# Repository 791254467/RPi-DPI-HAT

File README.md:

# RPi-DPI-HAT
Raspberry Pi HAT (Hardware Attached on Top) for TFT-Displays with DPI (Display Parallel Interface).

## Shop
* [RPi-DPI-HAT for TFT-Displays](http://www.watterott.com/en/RPi-DPI-HAT)
* [40-Pin FFC-Cable Extenter](http://www.watterott.com/en/40-Pin-FFC-extenter)
* [Bundle: RPi-DPI-HAT + 5" 800x480 Display without Touchpanel](http://www.watterott.com/en/5-800x480-RPi-DPI-HAT)
* Compatible TFT-Displays (Touchpanel cannot be used):
  * [5" 800x480 Display without Touchpanel](http://www.watterott.com/en/5-800x480-TFT-Display-without-TP)
  * [5" 800x480 Display with resitive Touchpanel](http://www.watterott.com/en/5-800x480-TFT-Display)
  * [7" 800x480 Display with resitive Touchpanel](http://www.watterott.com/en/7-800x480-TFT-Display)

## Features
* 40pin connector for TFT-Display
* LED Backlight Boost Regulator (up to 35V)
* Single 5V Power Supply via GPIO connector
* Note: The HDMI and video output cannot be used at the same time with a DPI display.

## Hardware
* [Schematics + Layout](https://github.com/watterott/RPi-DPI-HAT/tree/master/hardware)

## Software
* Install device tree blob ([originally from Robert Ely](https://github.com/robertely/dpi666)):
    ```
    $ sudo apt-get install device-tree-compiler
    $ wget -N https://raw.github.com/watterott/RPi-DPI-HAT/master/docu/dt-blob-dpi.dts
    $ sudo dtc -I dts -O dtb -o /boot/dt-blob.bin dt-blob-dpi.dts
    ```

* Open the file ```/boot/config.txt``` and add the following lines at the file end:
    ```
    $ sudo nano /boot/config.txt
    ```
    ```
    # disable SPI and I2C
    dtparam=spi=off
    dtparam=i2c_arm=off
    
    # enable 800x480 display (TFT050-3, TFT070-4)
    enable_dpi_lcd=1
    display_default_lcd=1
    dpi_group=2
    dpi_mode=87
    dpi_output_format=454661
    hdmi_ignore_edid=0xa5000080
    hdmi_cvt=800 480 60 6 0 0 0
    
    # 0 degrees - normal
    #display_rotate=0
    # 90 degrees
    #display_rotate=1
    # 180 degrees
    #display_rotate=2
    # 270 degrees
    #display_rotate=3
    # horizontal flip
    #display_rotate=0x10000
    # vertical flip
    #display_rotate=0x20000
    ```

* Reboot the system:
    ```
    $ sudo reboot
    ```

    *If there are problems then check, that you have not bootloader version 1.20150923, which has a bug. Upgrade the system with ```sudo apt-get update``` and ```sudo apt-get upgrade```.*

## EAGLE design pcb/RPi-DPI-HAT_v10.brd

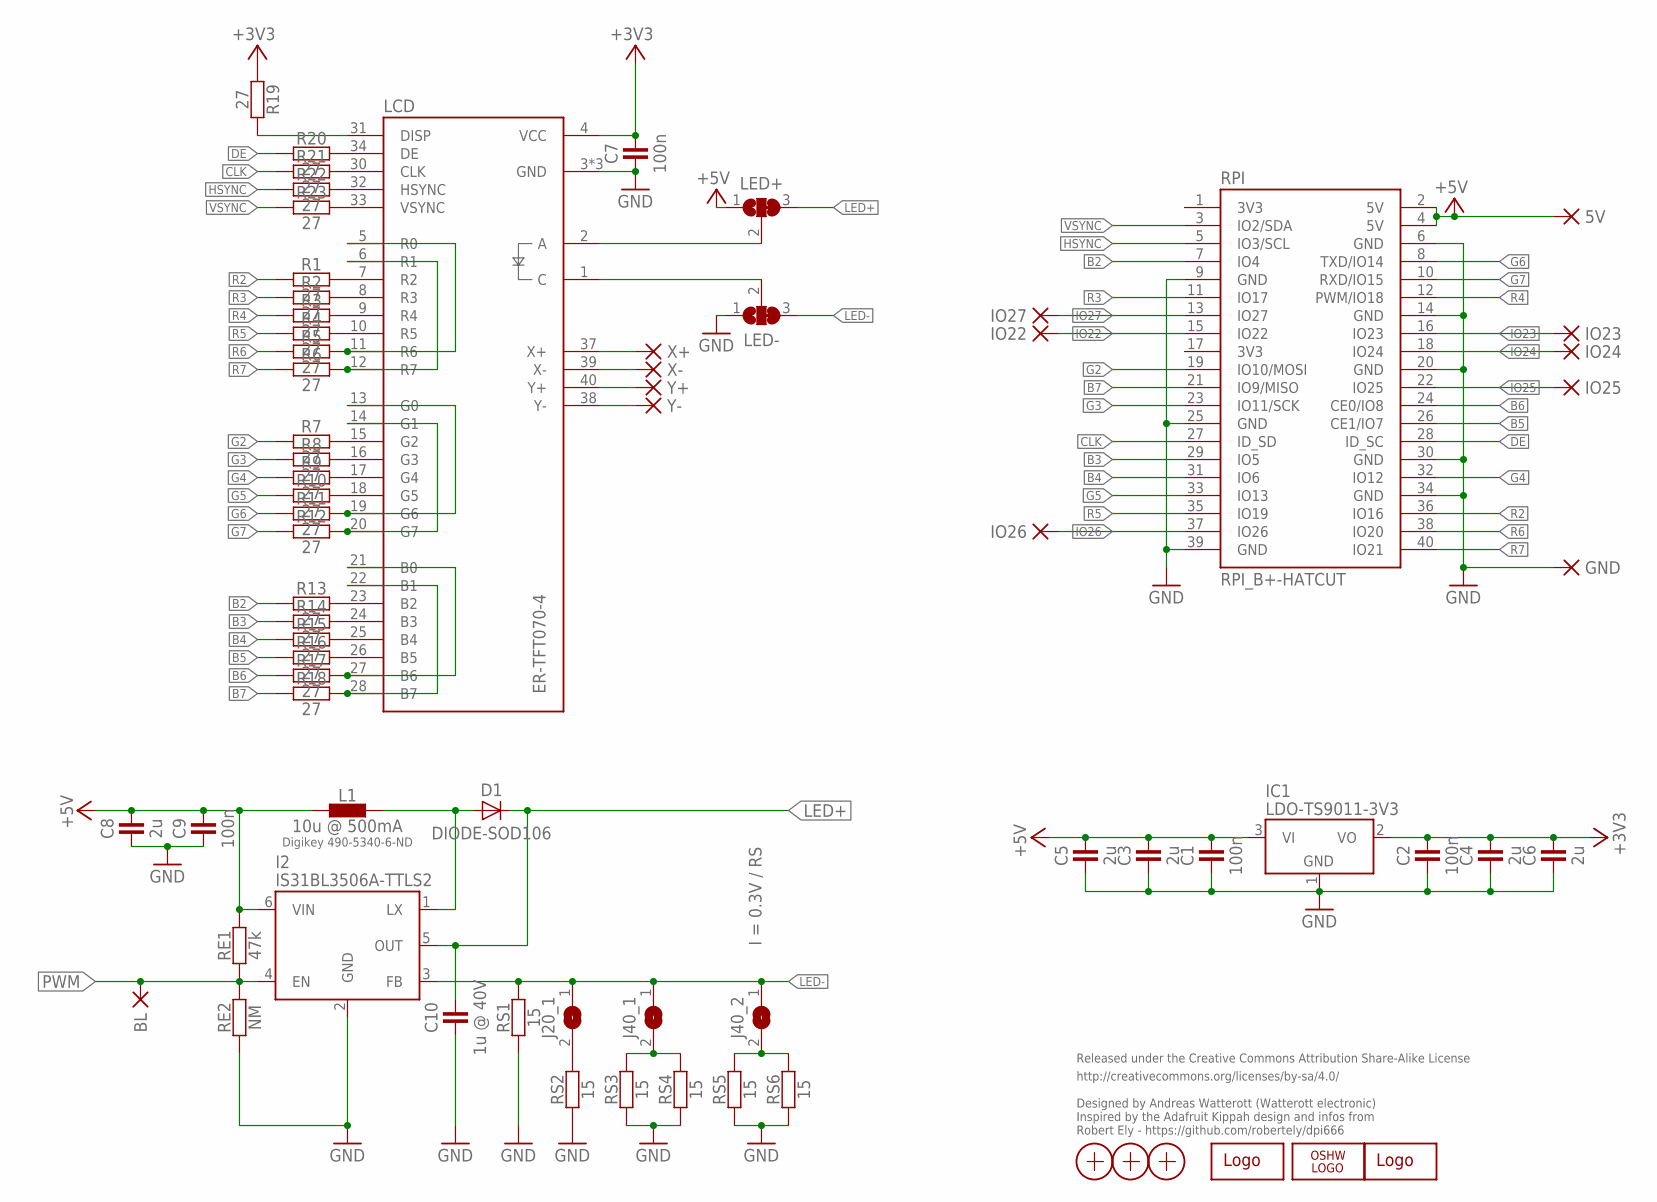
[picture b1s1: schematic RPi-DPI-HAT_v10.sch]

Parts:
5V: PAD-0.80X1.60_NC
BL: PAD-0.80X1.60_NC
C1, C2, C7, C9: 100n; C0402
C3, C4, C5, C6, C8: 2u; C0402
C10: 1u @ 40V; C0805
D1: DIODE-SOD106; SOD106
GND: PAD-0.80X1.60_NC
I2: IS31BL3506A-TTLS2; SOT23-6
IC1: LDO-TS9011-3V3; SOT23
IO22, IO23, IO24, IO25, IO26, IO27: PAD-0.80X1.60_NC
J20_1, J40_1, J40_2: JUMPER2-0402
L1: 10u @ 500mA; L_1212
LCD: ER-TFT070-4; FPC40
LED+: JUMPER3-0603-NC; JUMPER3-0603_NC
LED-: JUMPER3-0603-NC; JUMPER3-0603_NC
LOGO1: LOGO-S_PLACE_S; SPARK_TPLACE_S
LOGO2: OSHW_LOGOX0070; OSHW_6X70
LOGO3: LOGO-PLACE; LOGO_TPLACE
R1, R2, R3, R4, R5, R6, R7, R8, R9, R10, R11, R12, R13, R14, R15, R16, R17, R18, R19, R20, R21, R22, R23: 27; C0402
RE1: 47k; C0402
RE2: NM; C0402
RPI: RPI_B+-HATCUT; RPI-B+HAT_CUTOUT
RS1, RS2, RS3, RS4, RS5, RS6: 15; C0402
X1, X2, X3: PASSER-07; PASSER_07MM
X+: PAD-0.80X1.60_NC
X-: PAD-0.80X1.60_NC
Y+: PAD-0.80X1.60_NC
Y-: PAD-0.80X1.60_NC

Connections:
+3V3: C2.2, C4.2, C6.2, C7.2, IC1.2 (VO), LCD.4 (VCC), R19.1
+5V: 5V.1, C1.2, C3.2, C5.2, C8.2, C9.2, I2.6 (VIN), IC1.3 (VI), L1.1, LED+.1, RE1.2, RPI.2 (5V), RPI.4 (5V)
A: LCD.2 (A), LED+.2
B2: R13.1, RPI.7 (IO4)
B3: R14.1, RPI.29 (IO5)
B4: R15.1, RPI.31 (IO6)
B5: R16.1, RPI.26 (CE1/IO7)
B6: R17.1, RPI.24 (CE0/IO8)
B7: R18.1, RPI.21 (IO9/MISO)
C: LCD.1 (C), LED-.2
CLK: R21.1, RPI.27 (ID_SD)
DE: R20.1, RPI.28 (ID_SC)
G2: R7.1, RPI.19 (IO10/MOSI)
G3: R8.1, RPI.23 (IO11/SCK)
G4: R9.1, RPI.32 (IO12)
G5: R10.1, RPI.33 (IO13)
G6: R11.1, RPI.8 (TXD/IO14)
G7: R12.1, RPI.10 (RXD/IO15)
GND: C1.1, C2.1, C3.1, C4.1, C5.1, C6.1, C7.1, C8.1, C9.1, C10.1, GND.1, I2.2 (GND), IC1.1 (GND), LCD.3 (GND), LCD.29 (GND), LCD.36 (GND), LED-.1, RE2.1, RPI.6 (GND), RPI.9 (GND), RPI.14 (GND), RPI.20 (GND), RPI.25 (GND), RPI.30 (GND), RPI.34 (GND), RPI.39 (GND), RS1.1, RS2.1, RS3.1, RS4.1, RS5.1, RS6.1
HSYNC: R22.1, RPI.5 (IO3/SCL)
IO22: IO22.1, RPI.15 (IO22)
IO23: IO23.1, RPI.16 (IO23)
IO24: IO24.1, RPI.18 (IO24)
IO25: IO25.1, RPI.22 (IO25)
IO26: IO26.1, RPI.37 (IO26)
IO27: IO27.1, RPI.13 (IO27)
LED+: C10.2, D1.C, I2.5 (OUT), LED+.3
LED-: I2.3 (FB), J20_1.1, J40_1.1, J40_2.1, LED-.3, RS1.2
LX: D1.A, I2.1 (LX), L1.2
unnamed: J40_1.2, RS3.2, RS4.2
unnamed: J20_1.2, RS2.2
unnamed: LCD.7 (R2), R1.2
unnamed: LCD.5 (R0), LCD.11 (R6), R5.2
unnamed: J40_2.2, RS5.2, RS6.2
unnamed: LCD.6 (R1), LCD.12 (R7), R6.2
unnamed: LCD.8 (R3), R2.2
unnamed: LCD.9 (R4), R3.2
unnamed: LCD.10 (R5), R4.2
unnamed: LCD.15 (G2), R7.2
unnamed: LCD.16 (G3), R8.2
unnamed: LCD.17 (G4), R9.2
unnamed: LCD.18 (G5), R10.2
unnamed: LCD.13 (G0), LCD.19 (G6), R11.2
unnamed: LCD.14 (G1), LCD.20 (G7), R12.2
unnamed: LCD.23 (B2), R13.2
unnamed: LCD.24 (B3), R14.2
unnamed: LCD.25 (B4), R15.2
unnamed: LCD.26 (B5), R16.2
unnamed: LCD.21 (B0), LCD.27 (B6), R17.2
unnamed: LCD.22 (B1), LCD.28 (B7), R18.2
unnamed: LCD.31 (DISP), R19.2
unnamed: LCD.34 (DE), R20.2
unnamed: LCD.30 (CLK), R21.2
unnamed: LCD.32 (HSYNC), R22.2
unnamed: LCD.33 (VSYNC), R23.2
PWM: BL.1, I2.4 (EN), RE1.1, RE2.2
R2: R1.1, RPI.36 (IO16)
R3: R2.1, RPI.11 (IO17)
R4: R3.1, RPI.12 (PWM/IO18)
R5: R4.1, RPI.35 (IO19)
R6: R5.1, RPI.38 (IO20)
R7: R6.1, RPI.40 (IO21)
VSYNC: R23.1, RPI.3 (IO2/SDA)
X+: LCD.37 (X+), X+.1
X-: LCD.39 (X-), X-.1
Y+: LCD.40 (Y+), Y+.1
Y-: LCD.38 (Y-), Y-.1

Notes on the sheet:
Released under the Creative Commons Attribution Share-Alike License
http://creativecommons.org/licenses/by-sa/4.0/
Designed by Andreas Watterott (Watterott electronic)
I = 0.3V / RS
Digikey 490-5340-6-ND
Inspired by the Adafruit Kippah design and infos from Robert Ely - https://github.com/robertely/dpi666

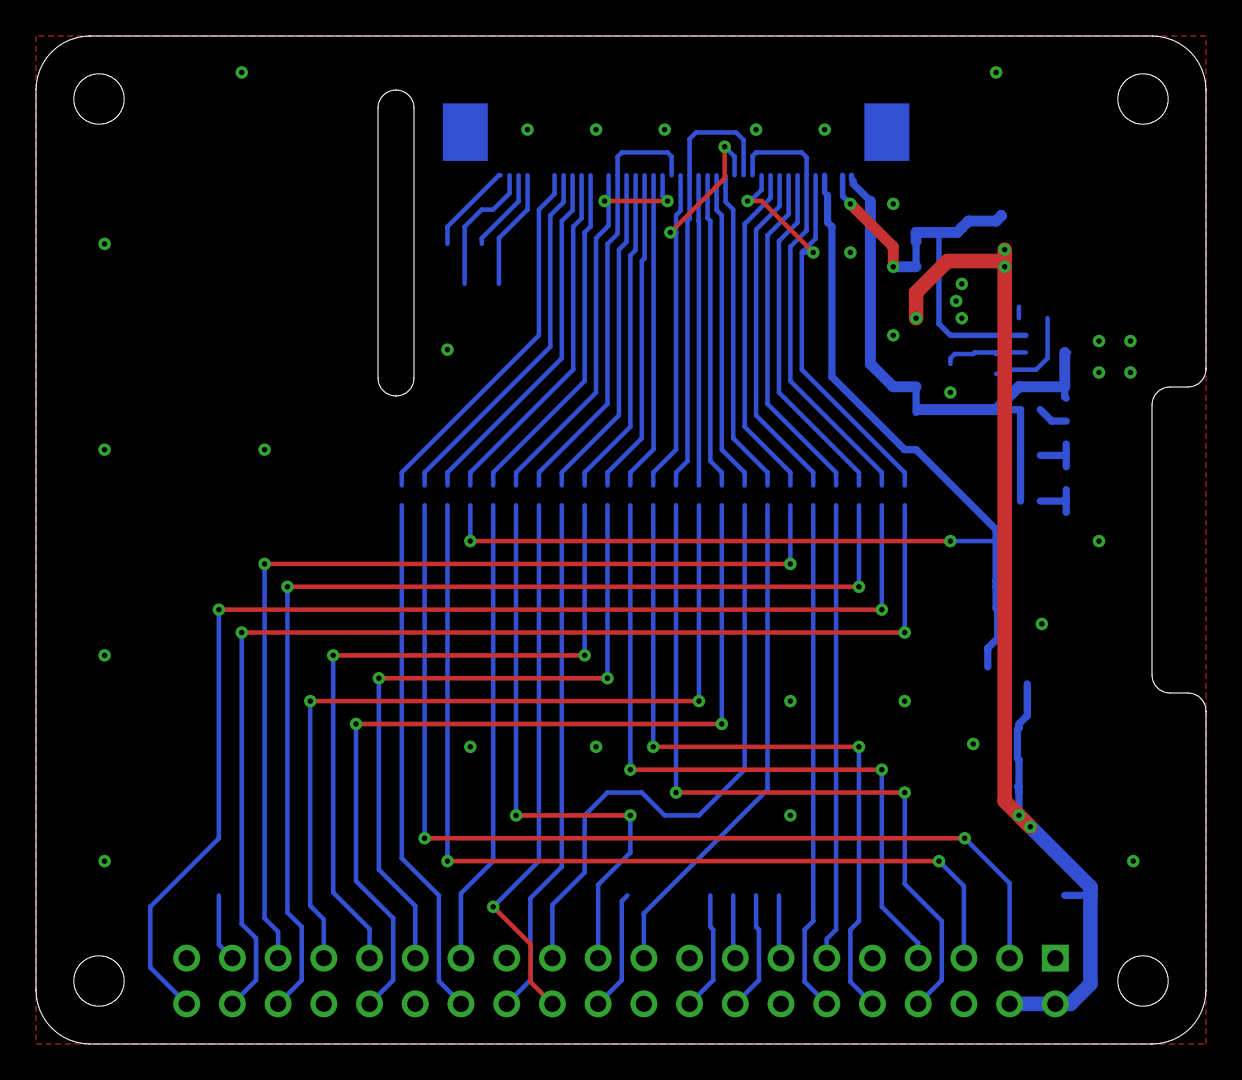
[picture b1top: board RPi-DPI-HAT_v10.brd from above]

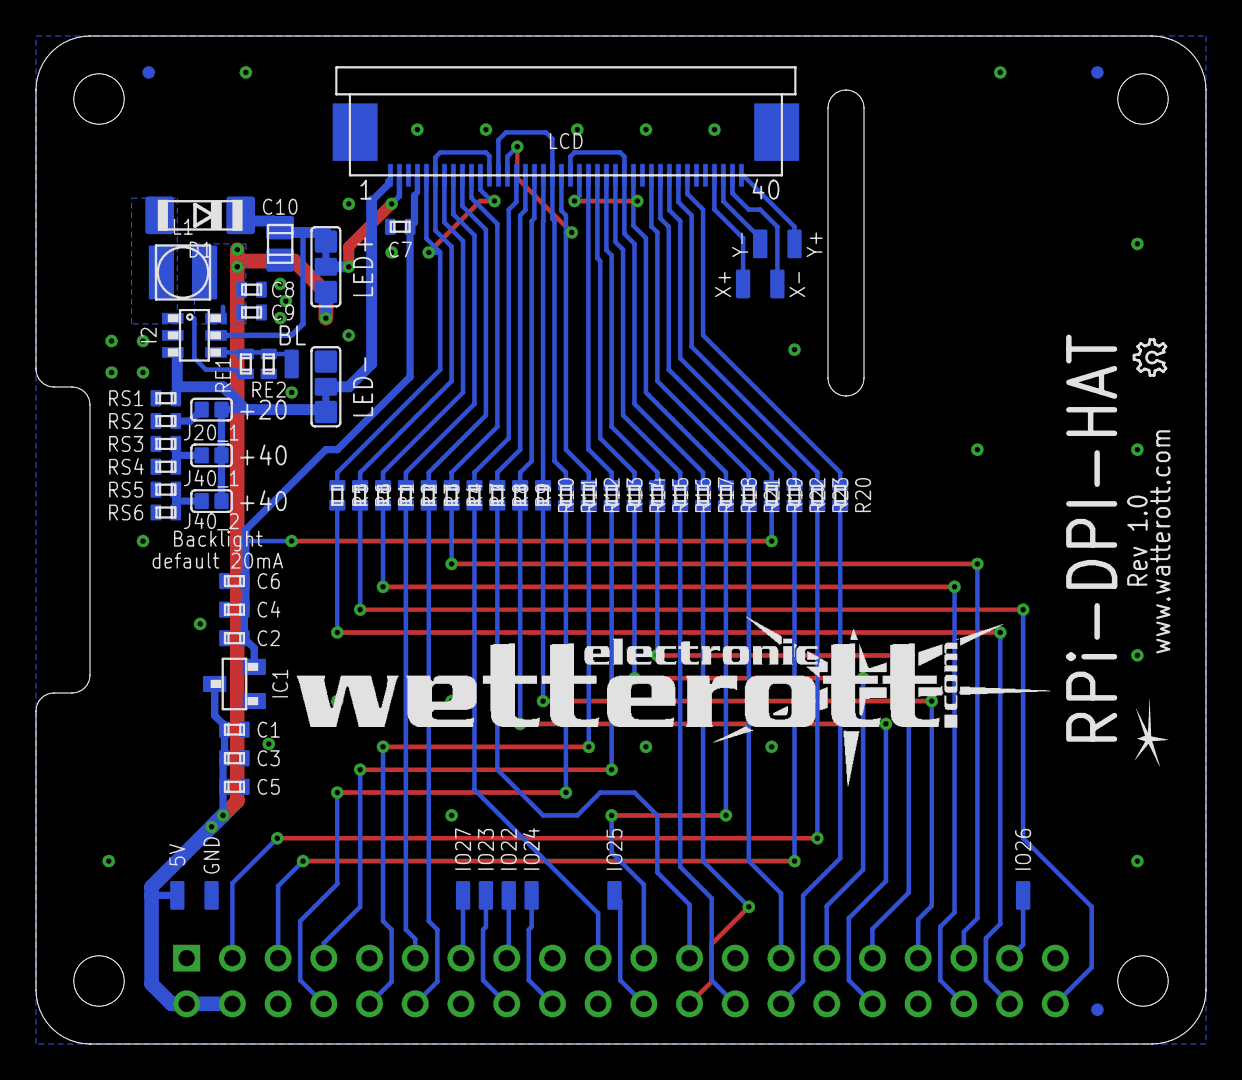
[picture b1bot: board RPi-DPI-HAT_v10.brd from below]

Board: 2 copper layers, 65.0 x 56.0 mm, 71 parts (70 on the bottom side), 67 nets.

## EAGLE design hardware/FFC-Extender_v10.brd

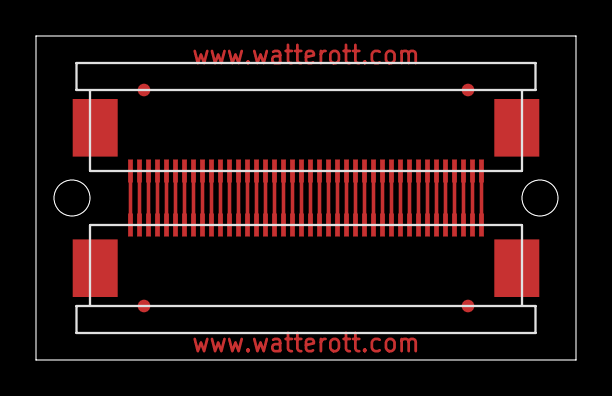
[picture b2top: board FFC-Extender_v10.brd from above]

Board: 2 copper layers, 30.0 x 18.0 mm, 6 parts (0 on the bottom side), 40 nets.

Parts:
J1, J2: FPC40
X1, X2, X3, X4: PASSER

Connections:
unnamed: J1.1, J2.40
unnamed: J1.2, J2.39
unnamed: J1.3, J2.38
unnamed: J1.4, J2.37
unnamed: J1.5, J2.36
unnamed: J1.6, J2.35
unnamed: J1.7, J2.34
unnamed: J1.8, J2.33
unnamed: J1.9, J2.32
unnamed: J1.10, J2.31
unnamed: J1.11, J2.30
unnamed: J1.12, J2.29
unnamed: J1.13, J2.28
unnamed: J1.14, J2.27
unnamed: J1.15, J2.26
unnamed: J1.16, J2.25
unnamed: J1.17, J2.24
unnamed: J1.18, J2.23
unnamed: J1.19, J2.22
unnamed: J1.20, J2.21
unnamed: J1.21, J2.20
unnamed: J1.22, J2.19
unnamed: J1.23, J2.18
unnamed: J1.24, J2.17
unnamed: J1.25, J2.16
unnamed: J1.26, J2.15
unnamed: J1.27, J2.14
unnamed: J1.28, J2.13
unnamed: J1.29, J2.12
unnamed: J1.30, J2.11
unnamed: J1.31, J2.10
unnamed: J1.32, J2.9
unnamed: J1.33, J2.8
unnamed: J1.34, J2.7
unnamed: J1.35, J2.6
unnamed: J1.36, J2.5
unnamed: J1.37, J2.4
unnamed: J1.38, J2.3
unnamed: J1.39, J2.2
unnamed: J1.40, J2.1

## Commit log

2015-05-28 added schematics and layout
2015-05-28 updated readme and docu
2015-08-21 changed path structure
2016-02-10 updated dt-blob-dpi
2016-04-10 updated schematics
2016-06-09 updated docu
